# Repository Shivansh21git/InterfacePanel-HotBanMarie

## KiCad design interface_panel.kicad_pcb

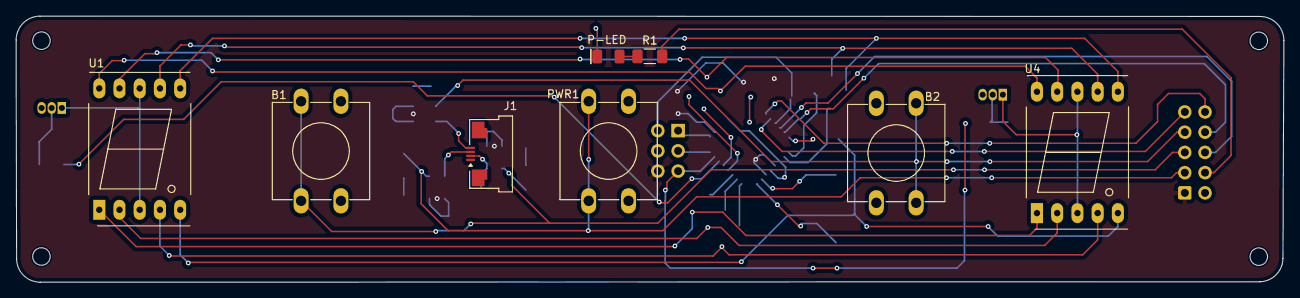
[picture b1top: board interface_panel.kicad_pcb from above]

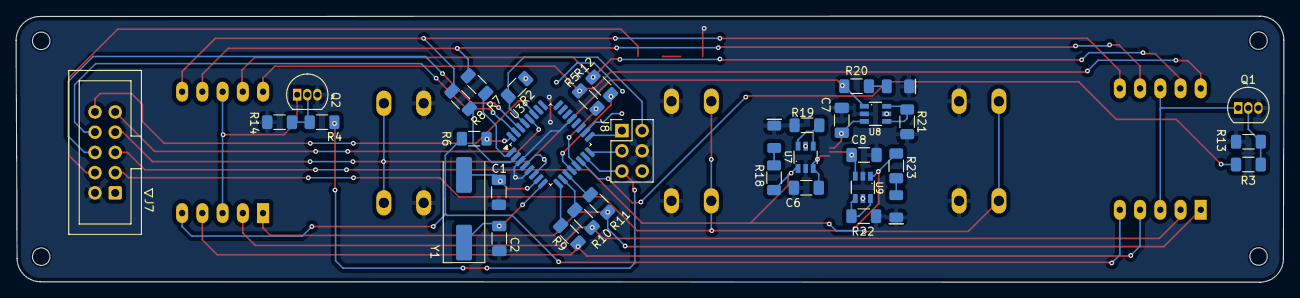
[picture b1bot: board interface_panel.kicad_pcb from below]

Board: 2 copper layers, 159.2 x 33.4 mm, 48 parts (36 on the bottom side), 47 nets.

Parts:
B1, B2: SW_Push; SW_PUSH-12mm
C1, C2, C6, C7, C8: C; C_1206_3216Metric_Pad1.33x1.80mm_HandSolder
D1, D5, D6, D7: LED; LED_1206_3216Metric
H1, H2, H3, H4: MountingHole; MountingHole_2.2mm_M2
J1: Conn_01x04_Pin; Amphenol_F32Q-1A7x1-11004_1x04-1MP_P0.5mm_Horizontal
J7: Conn_02x05_Odd_Even; IDC-Header_2x05_P2.54mm_Vertical
J8: `; PinHeader_2x03_P2.54mm_Vertical
PWR1: SW_Push; SW_PUSH-12mm
Q1, Q2: BC547; TO-92_Inline
R1, R3, R4, R5, R6, R7, R8, R9, R10, R11, R12, R13, R14, R18, R20, R23: R; R_1206_3216Metric_Pad1.30x1.75mm_HandSolder
R2, R19, R21, R22: 10k; R_1206_3216Metric_Pad1.30x1.75mm_HandSolder
U1, U4: SM420561N; 7SegmentLED_LTS6760_LTS6780
U3: ATmega328P-A; TQFP-32_7x7mm_P0.8mm
U7, U8, U9: TTP223-BA6; SOT23-6
Y1: Crystal; Crystal_SMD_HC49-SD

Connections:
5V: J7.1, J8.6, R2.1, U3.4 (VCC), U3.6 (VCC), U3.18 (AVCC), U7.5 (VDD), U8.5 (VDD), U9.5 (VDD)
/A4: J7.10, U3.27 (PC4)
/A5: J7.9, U3.28 (PC5)
/K1: B1.2, J7.5, R18.2, U7.1 (Q)
/K2: B2.2, J7.7, R20.2, U8.1 (Q)
/K3: J7.3, PWR1.2, R23.2, U9.1 (Q)
/TJ1: C6.2, J1.2, U7.3 (I)
/TJ2: C7.2, J1.4, U8.3 (I)
/TJ3: C8.2, J1.3, U9.3 (I)
/miso: J8.3, U3.16 (PB4)
/mosi: J8.5, R4.1, U3.15 (PB3)
/reset: J8.2, R2.2, U3.29 (~RESET/PC6)
A: R7.2, U1.7 (A), U4.7 (A)
B: R8.2, U1.6 (B), U4.6 (B)
C: R9.2, U1.4 (C), U4.4 (C)
CC1: Q1.2 (B), R3.2, R13.2
CC2: Q2.2 (B), R4.2, R14.2
D: R10.2, U1.2 (D), U4.2 (D)
D13: J8.1, U3.17 (PB5)
DPX: R6.2, U1.5 (DP), U4.5 (DP)
E: R11.2, U1.1 (E), U4.1 (E)
F: R12.2, U1.9 (F), U4.9 (F)
G: R5.2, U1.10 (G), U4.10 (G)
GND: B1.1, B2.1, C1.2, C2.2, C6.1, C7.1, C8.1, D1.1 (K), D5.1 (K), D6.1 (K), D7.1 (K), J7.2, J8.4, PWR1.1, Q1.3 (E), Q2.3 (E), R13.1, R14.1, R19.2, R21.2, R22.2, U3.3 (GND), U3.5 (GND), U3.21 (GND), U7.2 (VSS), U8.2 (VSS), U9.2 (VSS)
unnamed: D1.2 (A), R1.1
unnamed: D5.2 (A), R18.1
unnamed: D6.2 (A), R20.1
unnamed: D7.2 (A), R23.1
unnamed: Q1.1 (C), U1.3 (CC), U1.8 (CC)
unnamed: Q2.1 (C), U4.3 (CC), U4.8 (CC)
unnamed: R12.1, U3.12 (PB0)
unnamed: R5.1, U3.13 (PB1)
unnamed: R3.1, U3.14 (PB2)
unnamed: R6.1, U3.32 (PD2)
unnamed: R7.1, U3.1 (PD3)
unnamed: R8.1, U3.2 (PD4)
unnamed: R9.1, U3.9 (PD5)
unnamed: R10.1, U3.10 (PD6)
unnamed: R11.1, U3.11 (PD7)
unnamed: C1.1, U3.7 (XTAL1/PB6), Y1.2
unnamed: C2.1, U3.8 (XTAL2/PB7), Y1.1
unnamed: R19.1, U7.4 (AHLB), U7.6 (TOG)
unnamed: R21.1, U8.4 (AHLB), U8.6 (TOG)
unnamed: R22.1, U9.4 (AHLB), U9.6 (TOG)
RX: J7.6, U3.30 (PD0)
S. LED: J7.4, R1.2
TX: J7.8, U3.31 (PD1)

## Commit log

2024-10-26 inittial commit -- blank project
2024-10-26 oled symbol with connector
2024-10-26 button added
2024-10-26 ----New oled symbol added ----signal led added ----jack added
2024-10-26 same
2024-10-26 Footprint added Pcb updated
2024-10-26 PCB saved
2024-11-09 panel_final
2024-11-22 round tracks
2024-11-26 adjusted layout with bom & gerber files
2024-11-28 display and overall layout changed
2025-04-17 changed layout with 12mm push_but
2025-06-27 production level changes -1
2025-07-01 production change-2
2025-08-26 oled Production
2025-09-11 7segment added
2025-09-17 updated again
2025-09-17 Segment-added
2025-12-04 Interface Panel with 7-segment display along with 3 user switch to adjust the temperature and controlling the machine
2025-12-04 3dfiles
2026-02-10 new-layout with 7seg and fpc connector
2026-02-10 unrouted tracks - A4,A5
2026-02-11 fully routed pcb- just unarranged silk layers
2026-02-11 plot added
2026-02-11 redimensioned
2026-02-19 Fixed- schematics -atmega symbol
2026-02-19 fully routed with TH-atmega
2026-02-19 board dimension plot
2026-02-19 dimension plot
2026-02-19 board issue- fixed
2026-02-19 silkscreen fix
2026-03-20 fixes
2026-03-20 updated on 20-03-26
2026-04-03 updated as on 03-04-26
